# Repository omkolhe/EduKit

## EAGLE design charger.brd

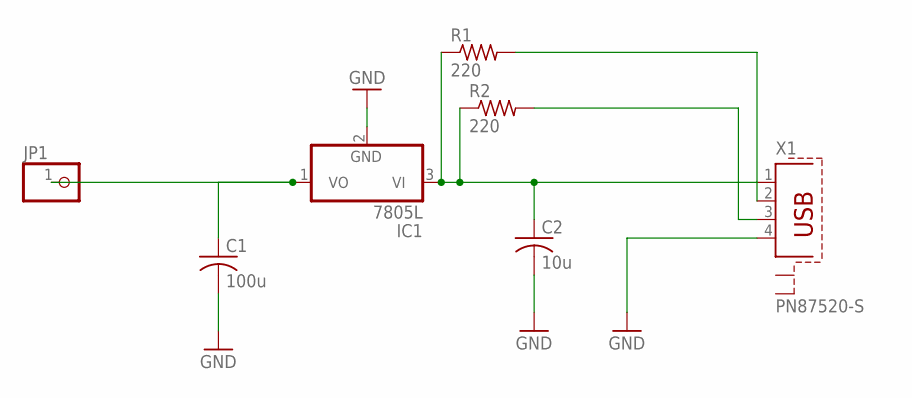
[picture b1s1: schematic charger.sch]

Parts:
C1: 100u; C025-040X050
C2: 10u; C025-040X050
IC1: 7805L; TO92
JP1: PINHD-1X1; 1X01
R1, R2: 220; 0204/7
X1: PN87520-S

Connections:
GND: C1.2, C2.2, IC1.2 (GND), X1.4
unnamed: C1.1, IC1.1 (VO), JP1.1
unnamed: C2.1, IC1.3 (VI), R1.1, R2.1, X1.1
unnamed: R1.2, X1.2
unnamed: R2.2, X1.3

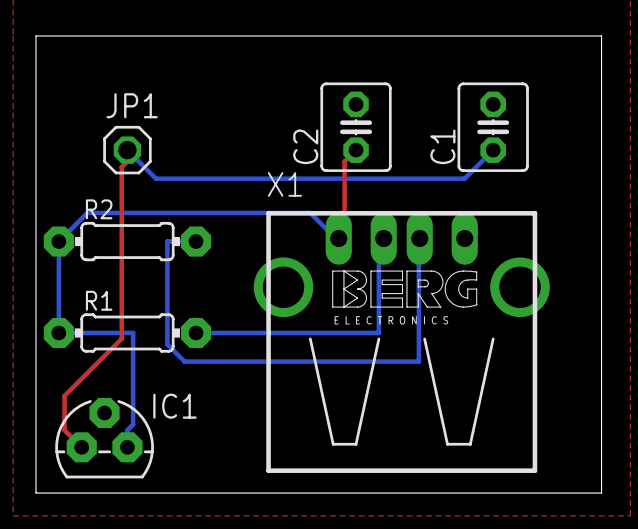
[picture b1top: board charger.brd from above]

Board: 2 copper layers, 31.4 x 25.4 mm, 7 parts (0 on the bottom side), 5 nets.

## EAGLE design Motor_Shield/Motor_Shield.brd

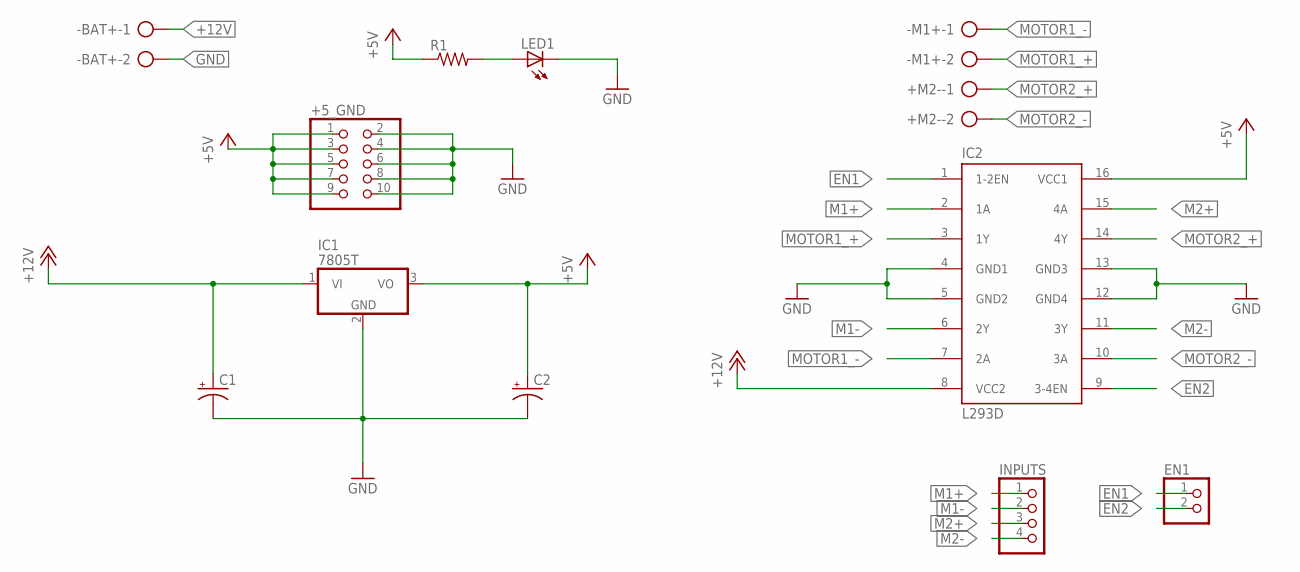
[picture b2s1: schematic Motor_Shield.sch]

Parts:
+5_GND: PINHD-2X5; 2X05
+M2-: AK500/2-H
-BAT+: AK500/2-H
-M1+: AK500/2-H
C1, C2: CPOL-USB45181A; B45181A
EN1: PINHD-1X2; 1X02
IC1: 7805T; TO220H
IC2: L293D; DIL16
INPUTS: PINHD-1X4; 1X04
LED1: LED5MM
R1: R-US_0309/12; 0309/12

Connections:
+5V: +5_GND.1, +5_GND.3, +5_GND.5, +5_GND.7, +5_GND.9, C2.+, IC1.3 (VO), IC2.16 (VCC1), R1.1
+12V: -BAT+.1, C1.+, IC1.1 (VI), IC2.8 (VCC2)
EN1: EN1.1, IC2.1 (1-2EN)
EN2: EN1.2, IC2.9 (3-4EN)
GND: +5_GND.2, +5_GND.4, +5_GND.6, +5_GND.8, +5_GND.10, -BAT+.2, C1.-, C2.-, IC1.2 (GND), IC2.4 (GND1), IC2.5 (GND2), IC2.12 (GND4), IC2.13 (GND3), LED1.K (C)
M1+: IC2.2 (1A), INPUTS.1
M1-: IC2.6 (2Y), INPUTS.2
M2+: IC2.15 (4A), INPUTS.3
M2-: IC2.11 (3Y), INPUTS.4
MOTOR1_+: -M1+.2, IC2.3 (1Y)
MOTOR1_-: -M1+.1, IC2.7 (2A)
MOTOR2_+: +M2-.1, IC2.14 (4Y)
MOTOR2_-: +M2-.2, IC2.10 (3A)
unnamed: LED1.A, R1.2

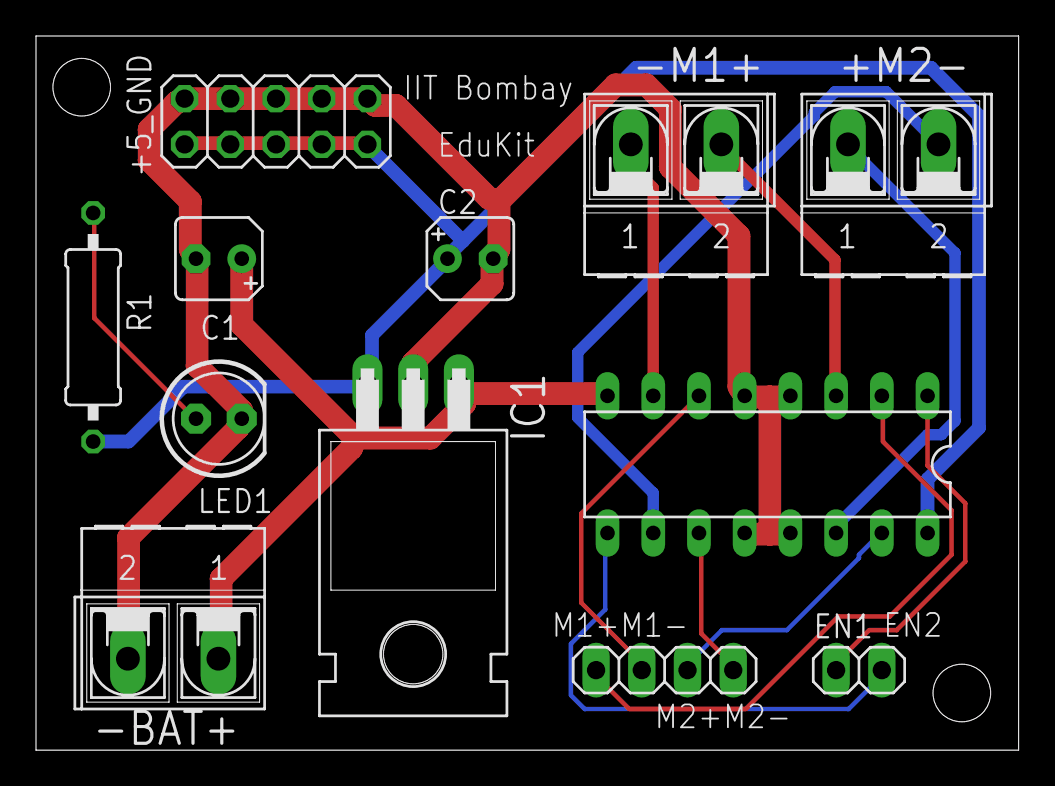
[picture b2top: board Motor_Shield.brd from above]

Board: 2 copper layers, 54.6 x 39.7 mm, 12 parts (0 on the bottom side), 14 nets.

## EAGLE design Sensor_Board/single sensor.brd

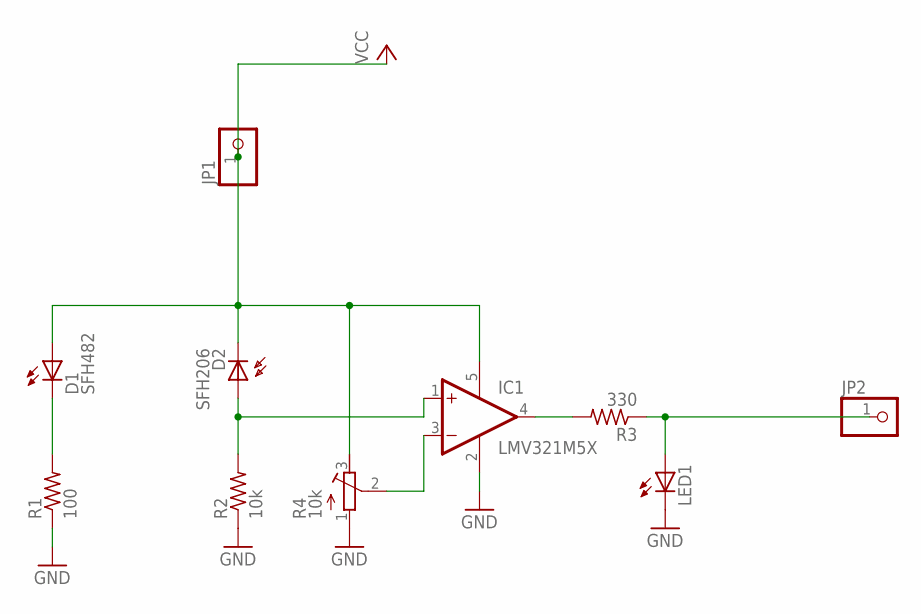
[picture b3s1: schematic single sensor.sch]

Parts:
D1: SFH482
D2: SFH206
IC1: LMV321M5X; SOT23-5
JP1, JP2: PINHD-1X1; 1X01
LED1: LED5MM
R1: 100; 0207/7
R2: 10k; 0207/7
R3: 330; 0207/7
R4: 10k; RTRIM5X

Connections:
GND: IC1.2 (V-), LED1.K (C), R1.1, R2.1, R4.1 (A)
unnamed: D1.K (C), R1.2
unnamed: D2.A, IC1.1 (+IN), R2.2
unnamed: IC1.3 (-IN), R4.2 (S)
unnamed: IC1.4 (OUT), R3.2
unnamed: JP2.1, LED1.A, R3.1
VCC: D1.A, D2.K (C), IC1.5 (V+), JP1.1, R4.3 (E)

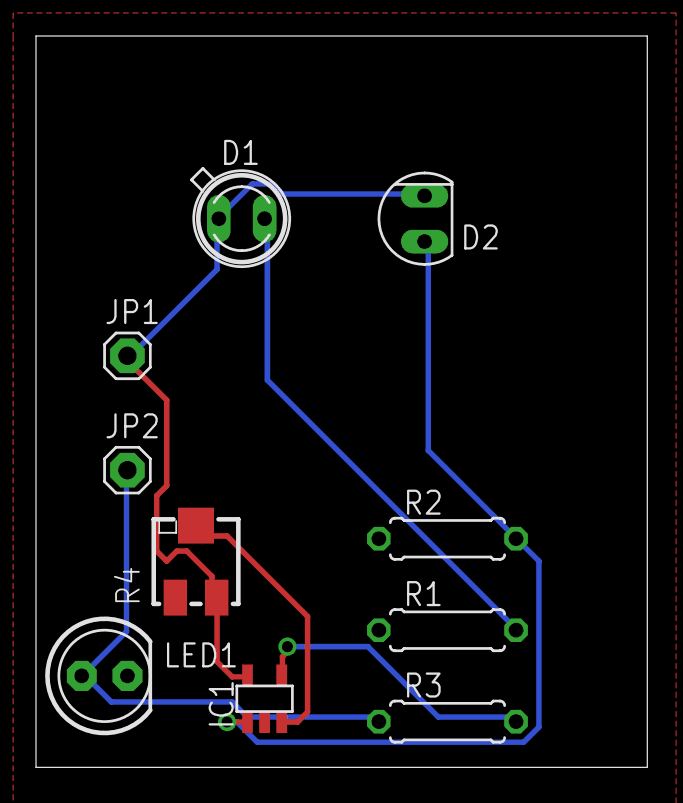
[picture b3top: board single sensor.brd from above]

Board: 2 copper layers, 34.0 x 40.6 mm, 10 parts (0 on the bottom side), 7 nets.

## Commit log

2017-05-27 Script for gesture controlled mouse simulator
    We will be modifying this script to control our bot
2017-05-29 Prints directions in accordance with gestures
2017-05-30 First Code for GCBot
2017-05-30 Updated GC-Bot programs
2017-05-30 First Code for GCBot IP
2017-05-30 Rename GCBot.py to GestureControlledBot/GCBot.py
2017-05-30 Rename GCBot_arduino.ino to GestureControlledBot/GCBot_arduino.ino
2017-05-30 Rename Manimouse.py to GestureControlledBot/Manimouse.py
2017-05-30 Snippet for opening COM port for bluetooth module
2017-05-30 Moved to a folder for opening it in Arduino IDE
2017-05-30 Added connection instructions
2017-05-31 arduino code without PID
2017-05-31 Moved to a folder
2017-06-01 Added the Board Files for Motor Shield
2017-06-02 single sensor
2017-06-05 Rename single sensor.brd to Sensor_Board/single sensor.brd
2017-06-05 Rename single sensor.sch to Sensor_Board/single sensor.sch
2017-06-06 Sample Code
2017-06-06 Changed Net Classes
2017-06-06 Added drill holes
2017-06-07 dynamo charger
